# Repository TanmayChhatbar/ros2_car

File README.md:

# ROS2-car (WIP) (0% Complete)

[README_ELI5](./README_ELI5.md)

## Goal

- Simultaneous Localization and Mapping (SLAM)
- Autonomous drifting capabilities

## Hardware Components

- **Desktop with ROS2**
  - Image recognition
  - SLAM
  - Planning
  - Miscellaneous computationally heavy processing
- **Raspberry Pi for Remote Control**
  - Remote control operation
  - Sensor to ROS publishing
  - Low-level, high-frequency control (VDC) (could be offloaded to ESP32)
- **Vehicle**
  - TT02 chassis for the autonomous car
  - Battery for car
  - Power bank for powering onboard electronics

## Targets

- Validation in simulation
  - Simulation for an AWD vehicle with a differential and drifting capabilities.
- Control development
  - PID Control
  - Machine Learning
- Deployment IRL
  - TT02 chassis

## Contributing

We welcome contributions from the community! If you have suggestions, improvements, or bug fixes, please feel free to submit a pull request or open an issue.

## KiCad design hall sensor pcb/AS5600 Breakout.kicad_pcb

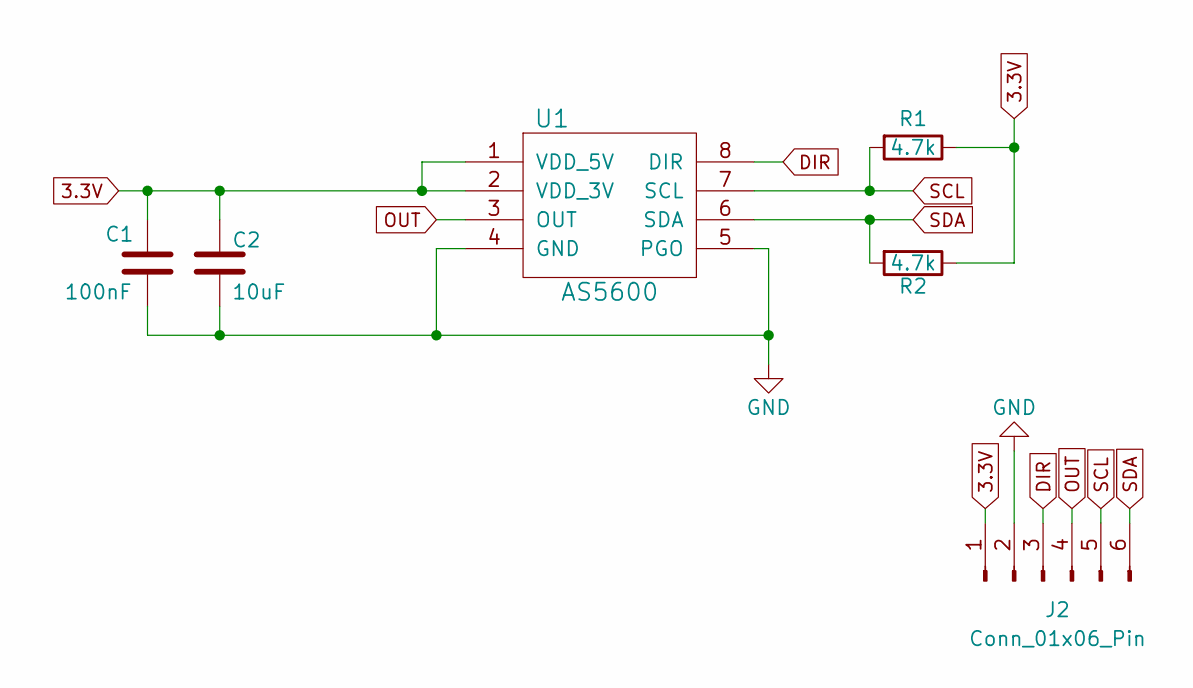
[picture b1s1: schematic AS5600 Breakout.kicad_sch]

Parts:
C1: 100nF; C_0805_2012Metric
C2: 10uF; C_0805_2012Metric
J2: Conn_01x06_Pin; PinHeader_2x03_P2.54mm_Vertical
R1, R2: 4.7k; R_0805_2012Metric
U1: AS5600; JEITA_SOIC-8_3.9x4.9mm_P1.27mm; Manufacturer Part Number AS5600-ASOM

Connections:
3.3V: C1.1, C2.1, J2.1, R1.1, R2.1, U1.1 (VDD_5V), U1.2 (VDD_3V)
DIR: J2.3, U1.8 (DIR)
GND: C1.2, C2.2, J2.2, U1.4 (GND), U1.5 (PGO)
OUT: J2.4, U1.3 (OUT)
SCL: J2.5, R1.2, U1.7 (SCL)
SDA: J2.6, R2.2, U1.6 (SDA)

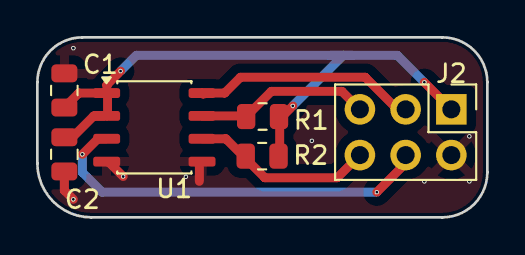
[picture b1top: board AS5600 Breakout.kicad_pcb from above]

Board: 2 copper layers, 25.0 x 10.0 mm, 6 parts (0 on the bottom side), 6 nets.

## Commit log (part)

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2025-04-13 init
2025-04-14 urdf and meshes with suspension
2025-04-14 add raw urdf mesh files
2025-04-14 add WIP ELI5 Readme
2025-04-15 add ros gitignore
2025-04-15 urdf with suspension, meshes and raw files
2025-04-16 init vehicle_sim package
2025-04-16 vehicle_sim init code
2025-04-18 add calculator functions for 2D vehicle_sim
2025-04-19 mid progress TODO
2025-04-24 readme update - pi camera v3 working on ubuntu 24.04, Raspberry Pi 5
2025-04-26 readme update - libcamera support for ROS2
2025-05-07 ELI5 readme rearrangement add joystick support section
2025-05-07 simulation - v0.1 - initialize vehicle_sim library
    ROS - initialize package vehicle_sim
2025-05-07 simulation - v0.2 - planar stable, not realistic simulation - PID control library octave - pacejka curve octave - plotting sim output
2025-05-07 simulation - v0.3 - planar stable, realistic
    simulation - add cruise control library
    simulation - low-speed slip corrections
    simulation - add inline test case
    simulation - restructure classes in individual files
    simulation - add gear ratios
    simulation - add aero forces
2025-05-07 simulation - connect to ROS w/ joystick input
2025-05-07 simulation - publish PoseStamped message
2025-05-08 simulation - split node to cpp and hpp
2025-05-08 update TODO
2025-05-20 simulation - v0.4 - track wheel rotations
    simulation - warning suppression
2025-05-21 simulation - add performance profiling
2025-05-21 simulation - tire rolling and stiction resistance
2025-05-21 simulation - add drivetrain selection
2025-05-21 simulation - add negative torque at 0 throttle
2025-05-21 ROS - connect to ROS w/ joystick input
    update ELI5 readme
    update TODO
2025-05-23 init control map
2025-05-23 control - basic optimization solver
2025-05-23 solver - jacobian
2025-05-23 solver - RK4
2025-05-23 solver - check norm before limiting
2025-06-25 IO - generic CSVReader and CSVWriter
    output - generic CSVWriter
2025-06-25 octave - control map viz
    modify control map
    add option to plot wheelspeed ratio
2025-06-25 control map - make constants
    control map - steering assignment bugfix
    control map - minor update
2025-06-25 control map - common file, backup csvs
2025-06-25 control map - using nlopt
    refinement criteria
    rebase with previous
    better cout
    increase maxtime for opt
2025-06-25 control map - parallelize nlopt
2025-06-25 control map - using bruteSolver
    cmakelists - make stricter
    bruteSolver - refineable map
    control map - center search space
    ...on kinematic steering angle
    control map - recalc invalids
    control map - more conditions for refinement
2025-06-25 solver - init bruteforce solver
    parallelize
    minor opts
2025-06-25 control map - data
2025-10-28 init rpm hall sensor
2025-10-29 basic motor control works
2025-11-02 connection readme
2025-11-02 joystick to python
2025-11-02 servo control with PCA9685 init
2025-11-02 joystick to PCA9685 test
2025-11-02 test or old files
    rebase
2025-11-06 init
    remove export files rebase
    rebase 1
2025-11-06 make smaller, remove holes
    rebase 2
2025-11-07 imu init
2025-11-07 casadi - add submodule
    casadi - init control map
2025-11-07 casadi - test for vx map, not working
2025-11-09 imu over i2c works
2025-11-10 readme update
2025-11-10 add submodules for pi camera
2025-11-10 ros node for imu telemetry
2025-11-10 add offsets to angular velocity
2025-11-10 test code without ros
2025-11-10 remove sim files from pi branch
2025-11-10 stream using python
2025-11-12 remove vehicle_sim files from branch
2025-11-12 joystick pub, rqt_image_view launch file
2025-11-12 rename to xbox
2025-11-12 simagic control TODO
2025-11-14 minor param update
2025-11-14 note skip in readme
2025-11-14 update readme for sim
2025-11-18 imu to ros package, node
    imu better errors, test file
    change folder name - src to telemetry
    enable imu over i2c
    use alternate pins for imu
2025-11-18 add camera to telemetry
2025-11-18 pi reads joystick over ros
    specify camera image format
    control frame rate
2025-11-18 PCA9685 over ros works
    option to simulate servo if no PCA
    safety reset command
    print once if no pub
    pca test file
    minor changes. remote control works
2025-11-18 hall sensor init
    rebase
2025-11-19 python read simagic inputs
2026-04-07 add dt to cruise controller
2026-04-07 add stiction coeff to toyota 86
2026-04-07 matlab init but slow
2026-06-26 use symbolic
2026-06-30 basic global search
